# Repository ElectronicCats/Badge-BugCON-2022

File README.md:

# Badge BugCON 2022

El nuevo orden entrega esta insignia a sus seguidores mas asiduos, escucha nuestras instrucciones, dinos lo que deseas y observa como la seguridad solo es un mito!  

## Como Iniciar
- Conecta por medio de USB de Badge
- Utiliza una terminal serial para acceder al badge puedes usar "monitor" en Linux, Putty en Windows
- Selecciona el puerto serial correcto a 115200 baudios
- Observa como inicia la terminal
- Puedes escribir "help" para acceder a mas comandos

## Deseas programar con Arduino?

Visita la [Wiki del proyecto](https://github.com/ElectronicCats/Badge-BugCON-2022/wiki)

## Tecnologias utilizadas

- RP2040
- USB
- LEDs
- Microfono
- Buzzer o bocina
- Un poco, una cucharadita de Machine Learning, gracias a [EdgeImpulse](https://www.edgeimpulse.com/)

## Links

- [RP2040 con Arduino Mbed](https://github.com/arduino/ArduinoCore-mbed)

## Agradecimientos
¿Quieres dar las gracias? Etiqueta a estas empresas en redes sociales y muestrales tu badge, gracias a ellos es posible

- [BugCON](https://www.pcbway.com/)
- [ElectronicCats](https://electroniccats.com/)

## License

Electronic Cats hemos creado un badge electronico para BugCON2022 en la CDMX, bienvenidos a la #badgelive

Electronic Cats invests time and resources providing this open source design, please support Electronic Cats and open-source hardware by purchasing products from Electronic Cats!

Designed by Electronic Cats.

Hardware released under an CERN Open Hardware Licence v1.2. See the LICENSE_HARDWARE file for more information.

Electronic Cats is a registered trademark, please do not use if you sell these PCBs.

Nov 2022

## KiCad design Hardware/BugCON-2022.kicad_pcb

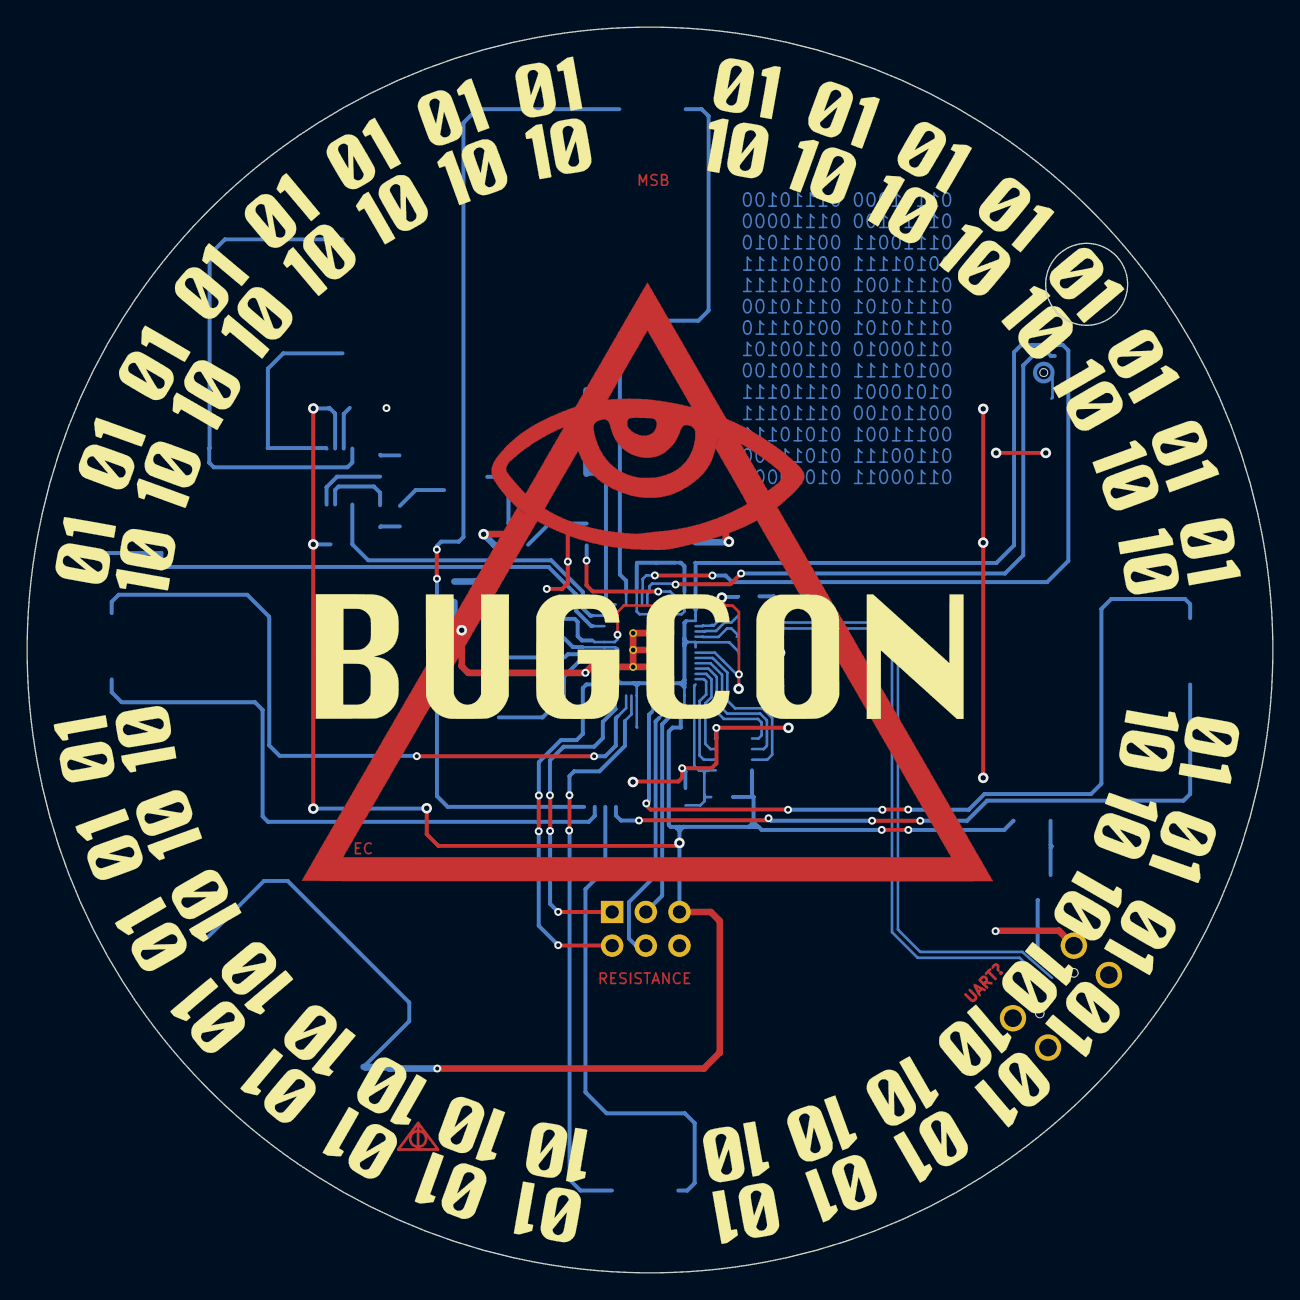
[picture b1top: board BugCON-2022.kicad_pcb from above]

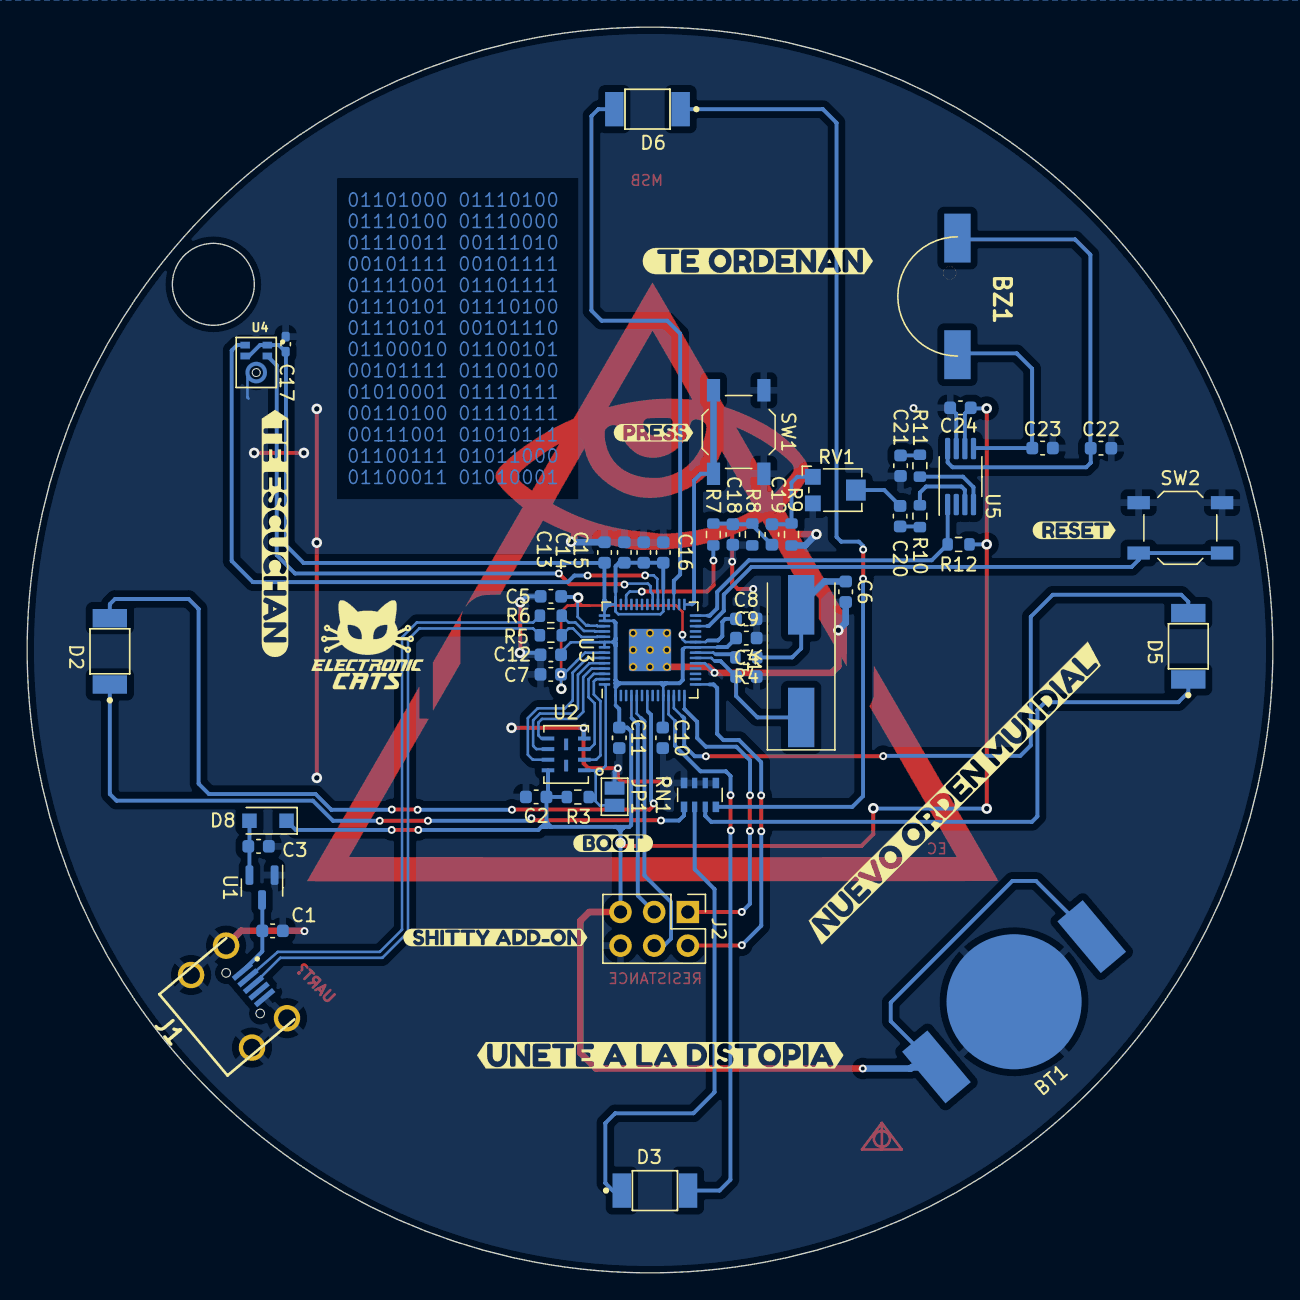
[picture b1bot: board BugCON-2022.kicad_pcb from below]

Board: 2 copper layers, 94.0 x 94.0 mm, 63 parts (62 on the bottom side), 45 nets.

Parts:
BT1: Battery_Cell; BAT-HLD-012-SMT-OTL
BZ1: Buzzer; CAPAE1050X250N
C1, C3, C24: 10uF; C_0603_1608Metric
C2, C7, C8, C10, C11, C12, C13, C14, C15, C16: 0.1uF; C_0603_1608Metric
C4, C6: 27pF; C_0603_1608Metric
C5, C9, C20, C21: 1uF; C_0603_1608Metric
C17: 0.1uF; C_0402_1005Metric_Pad0.74x0.62mm_HandSolder
C18: 100nF; C_0603_1608Metric
C19: 47uF; C_0603_1608Metric
C22, C23: 220pF; C_0603_1608Metric
D2, D3, D5, D6: R_LED; LYT77K-K2M1-NoHole
D8: SS1020FL; D_SOD-123F
J1: USB_B_Micro; U254051N4BH806
J2: Conn_02x03_Odd_Even; PinHeader_2x03_P2.54mm_Vertical
JP1: BOOT; SolderJumper-2_P1.3mm_Open_Pad1.0x1.5mm
R3, R12: 10K; R_0603_1608Metric
R4: 1K; R_0603_1608Metric
R5, R6: 27; R_0603_1608Metric
R7: 220; R_0603_1608Metric
R8, R10, R11: 100; R_0603_1608Metric
R9: 1.8K; R_0603_1608Metric
RN1: R_Pack04; R_Array_Convex_4x0603
RV1: 10K; Potentiometer_Bourns_TC33X_Vertical
Ref**: Val**; pin_final_cc
SW1: Button; SW_SPST_TL3342
SW2: RESET; SW_SPST_TL3342
U1: MCP1700-31; SOT-23
U2: W25Q16JV; W25Q16JVUUIQ
U3: RP2040; RP2040-QFN-56
U4: SPH0641LM4H; MIC_SPH0641LM4H-1
U5: PAM8302AAD; MSOP-8_3x3mm_P0.65mm
Y1: 12Mhz; Crystal_SMD_HC49-SD
kibuzzard-6340AD5F: G***; kibuzzard-6340AD5F
kibuzzard-63409D39: G***; kibuzzard-63409D39
kibuzzard-63409DA5: G***; kibuzzard-63409DA5
kibuzzard-63409DC5: G***; kibuzzard-63409DC5
kibuzzard-63409E53: G***; kibuzzard-63409E53
kibuzzard-63409EAE: G***; kibuzzard-63409EAE
kibuzzard-63409EDC: G***; kibuzzard-63409EDC
kibuzzard-63409F0B: G***; kibuzzard-63409F0B

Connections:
+1V2: C5.1, C7.1, C8.1, U3.23 (DVDD), U3.45 (VREG_VOUT), U3.50 (DVDD)
+3V3: BT1.2 (-), C2.1, C9.1, C10.1, C11.1, C12.1, C13.1, C14.1, C15.1, C16.1, C17.1, C24.1, D8.1 (K), J2.5, R3.1, R12.2, U2.8 (VCC), U3.1 (IOVDD), U3.10 (IOVDD), U3.22 (IOVDD), U3.33 (IOVDD), U3.42 (IOVDD), U3.43 (ADC_AVDD), U3.44 (VREG_IN), U3.48 (USB_VDD), U3.49 (IOVDD), U4.1 (VDD), U4.2 (LR), U5.6 (VDD)
/A2: R7.2, U3.40 (GPIO28_ADC2)
/CLK: U3.35 (GPIO23), U4.3 (CLK)
/D0: D2.2 (A), U3.7 (GPIO5)
/D5: D3.2 (A), U3.11 (GPIO8)
/D6: D5.2 (A), U3.12 (GPIO9)
/D10: J2.1, U3.14 (GPIO11)
/D11: J2.2, U3.15 (GPIO12)
/D12: D6.2 (A), U3.31 (GPIO20)
/D+: J1.3 (D+), R5.1
/D-: J1.2 (D-), R6.1
/DOUT: U3.34 (GPIO22), U4.4 (DOUT)
/GPIO17: R12.1, U3.28 (GPIO17), U5.1 (~SD)
/GPIO18: SW1.2, U3.29 (GPIO18)
/QSPI_CS: JP1.2 (B), R3.2, U2.1 (~CS), U3.56 (QSPI_SS)
/QSPI_DATA0: U2.5 (DI(IO0)), U3.53 (QSPI_SD0)
/QSPI_DATA1: U2.2 (DO(IO1)), U3.55 (QSPI_SD1)
/QSPI_DATA2: U2.3 (IO2), U3.54 (QSPI_SD2)
/QSPI_DATA3: U2.7 (IO3), U3.51 (QSPI_SD3)
/QSPI_SCK: U2.6 (CLK), U3.52 (QSPI_SCLK)
/RD+: R5.2, U3.47 (USB_DP)
/RD-: R6.2, U3.46 (USB_DM)
/RST: SW2.2, U3.26 (RUN)
/SCL: J2.4, U3.5 (GPIO3)
/SDA: J2.3, U3.4 (GPIO2)
GND: BT1.1 (+), C1.2, C2.2, C3.2, C4.2, C5.2, C6.2, C7.2, C8.2, C9.2, C10.2, C11.2, C12.2, C13.2, C14.2, C15.2, C16.2, C17.2, C18.2, C21.2, C22.2, C23.2, C24.2, J1.5 (GND), J1.6 (Shield), J2.6, JP1.1 (A), R8.2, R9.2, RN1.5 (R4.2), RN1.6 (R3.2), RN1.7 (R2.2), RN1.8 (R1.2), RV1.3, SW1.1, SW2.1, U1.1 (GND), U2.4 (GND), U3.19 (TESTEN), U3.57 (GND), U4.5 (GND), U5.7 (GND)
unnamed: BZ1.1 (-), C23.1, U5.5 (OUT+)
unnamed: BZ1.2 (+), C22.1, U5.8 (OUT-)
unnamed: C3.1, D8.2 (A), U1.2 (VO)
unnamed: C4.1, U3.20 (XIN), Y1.1
unnamed: C6.1, R4.1, Y1.2
unnamed: C18.1, C19.1, R7.1, R8.1
unnamed: C19.2, R9.1, RV1.1
unnamed: C20.1, RV1.2
unnamed: C20.2, R10.1
unnamed: C21.1, R11.1
unnamed: D2.1 (K), RN1.1 (R1.1)
unnamed: D3.1 (K), RN1.2 (R2.1)
unnamed: D5.1 (K), RN1.3 (R3.1)
unnamed: D6.1 (K), RN1.4 (R4.1)
unnamed: R4.2, U3.21 (XOUT)
unnamed: R10.2, U5.3 (IN+)
unnamed: R11.2, U5.4 (IN-)
VBUS: C1.1, J1.1 (VBUS), U1.3 (VI)

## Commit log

2022-11-15 El nuevo orden esta aqui
2022-11-17 Erased unnecesary files
2022-11-17 add example audio wav
2022-11-17 Changed Edge impulse link
2022-11-21 Add Pin ampli
2022-11-21 Disable ampli default
